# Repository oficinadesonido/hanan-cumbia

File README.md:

# HANAN CUMBIA · Batería electrónica (Arduino Nano)

Caja de ritmos / batería electrónica tropical de **Oficina de Sonido** (desde 2020). Plataforma
**Arduino Nano (ATmega328P)** + DAC externo **MCP4901** por SPI, síntesis por wavetable.
Dos versiones de hardware con **el mismo circuito y el mismo firmware**:

| Versión | PCB | Qué es |
|---|---|---|
| **Clásica** | `hardware/hananClasicaPcb/` | 77×92 mm, 8 pulsadores en placa, jack DC 9 V, va en caja. |
| **Mini** | `hardware/hananMiniPcb/` | 150×75 mm (= panel), calado para 4 botones arcade, se alimenta por USB. Para talleres. |

El rediseño 2026 en ESP32 es otro producto: `../hanan-mk2/`.

## 🔥 Web Flasher / Hanan Estudio

👉 **https://oficinadesonido.github.io/hanan-cumbia/webflasher/** (GitHub Pages desde `main`;
todo push a `main` queda publicado al toque). Chrome/Edge/Opera de escritorio (Web Serial).
`hananFabrica/` es el flasher de fábrica (solo firmware). Notas de diseño en `webflasher/README.md`.

## Estructura

```
hardware/hananClasicaPcb/   PCB clásica v2.0 (KiCad 10)      ← ver su README
hardware/hananMiniPcb/      PCB Mini v2.0 (KiCad 10)
firmware/hanan26Taller/     Firmware actual (Taller 2026; de acá salen los builds del Estudio)
firmware/tests/             Sketches de diagnóstico (DAC, potes, pines, motor de audio)
firmware/legacy/HTRCMB_10/  Firmware original del que deriva todo (histórico)
webflasher/                 Hanan Estudio + Lab + flasher (HTML/JS, STK500v1)
hananFabrica/               Flasher de fábrica
docs/                       Revisión eléctrica, capas EasyEDA, SVG de calados del panel Mini
```

Perfil de fabricación: **tht** (JLC solo PCB, se suelda en taller). Regla: toda placa lleva en silk
`<proyecto> vX.Y AAAA-MM-DD` = nombre del zip de gerbers (title block del PCB).

## Cambios v2.0 de ambas PCB (2026-10-07)
- RC en Vref del DAC (R6 1k + C2 10 µF) y 100 nF en Vdd (C3): el ruido del USB/cargador ya no entra
  directo a la referencia del audio. Pads del LED RGB agrandados. Rótulo de versión en silk.
- Mini: los 8 pads de los cables de los botones arcade pasan a una columna de pads grandes en pares
  (blanco/rosa/amarillo/verde + GND), zona GND en toda la placa.
- Detalle y pendientes en `docs/revision-electronica-mini.md` y `hardware/hananClasicaPcb/README.md`.

## Firmware: cambios respecto al original
- **Fix de tempo (pitch ⇒ BPM):** el secuenciador se clockeaba con `micros()`, que bajo la carga de la
  ISR de audio perdía tiempo. Ahora el tempo se cuenta con un reloj estable dentro de la ISR (`audioclock`).
- **BPM por defecto = 90**; **potenciómetros invertidos** (A0/A1); **A14 neutralizado** (solo 2 potes);
  **piso de pitch en A1** para que el sample siempre suene completo.

```bash
arduino-cli compile --fqbn arduino:avr:nano firmware/hanan26Taller
arduino-cli upload  --fqbn arduino:avr:nano -p /dev/ttyUSB0 firmware/hanan26Taller
```
Requiere el core `arduino:avr` y las librerías `Bounce` y `DAC_MCP49xx`.

## Historial
El material viejo (Placa_2021, HTR_2023, hanan25, audios, códigos, backups) se movió el 2026-10-07 a
`3-archivo/hanan-cumbia-historico/` (y está en el respaldo TOSHIBA). Repo viejo `oficinadesonido/HananCumbia` (2023).

---
🤖 Mantenido con ayuda de [Claude Code](https://claude.com/claude-code) · oficinadesonido.org

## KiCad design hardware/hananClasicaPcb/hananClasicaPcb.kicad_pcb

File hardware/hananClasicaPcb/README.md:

# hananClasicaPcb — Hanan Cumbia clásica, PCB principal v2.0 (2026-10-07)

Proyecto KiCad 10 armado el 2026-10-07 a partir de:
- **PCB:** `../hanan25.kicad_pcb` (77.1×92.1 mm; mismo diseño que `Hanan.kicad_pcb`/`Hanantaller.kicad_pcb`/`HTR_2023`;
  última fabricación JLC Y194, 10 u., 2025-11-14).
- **Esquemático:** copia de `hanan26/hananMiniPcb/hananMiniPcb.kicad_sch` (mismos refs y UUIDs que la PCB) +
  `J1` jack DC y `D2` diodo serie a `+9V`/VIN (net `VIN_JACK`). El `.sch` legacy `BD1.sch` queda como histórico.
  Los enlaces sch↔pcb coinciden (UUID de símbolo = path de huella), así que "Actualizar PCB desde esquemático" en el GUI
  no debería mover nada.

## Cambios v2.0 (iguales a hananMiniPcb v2.0)
- `R6` 1 kΩ + `C2` 10 µF: RC en Vref del MCP4901 (U1.6, net `VREF`); `C3` 100 nF en Vdd (U1.1). Cara B, borde izquierdo
  junto a R3 (R6 x=52.6, C2 x=51.8, C3 y=105.8). El +5C que entraba al pad 6 se cortó en (61.9,112.6) y se reruteó.
- Pads de `D1` (LED RGB) 1.25×1.8 mm (anillo 0.175 ≥ 0.13 JLC). Solo en la instancia del PCB.
- Title block (rev `v2.0`, fecha) + silk `hananClasicaPcb ${REVISION} ${ISSUE_DATE}` en F y B (y=160.6).
- DRC: 0 sin conectar, 0 errores. Warnings preexistentes: libs `OdeS`/`SWITCH`/`Arduino` no configuradas, silk al
  borde, textos XA1, vía colgada de `Net-(J2-Pad1)` en (113.3,149.7).

## Al fabricar
Fecha del title block = fecha de orden (sch y pcb) → zip `hananClasicaPcb-v2.0-<AAAA-MM-DD>.zip`.
Pendientes 🟡 (no incluidos): R serie en clock out, protección clock in, 10 nF de reconstrucción — ver
`hanan26/docs/revision-electronica-mini.md` (aplica igual a esta placa).

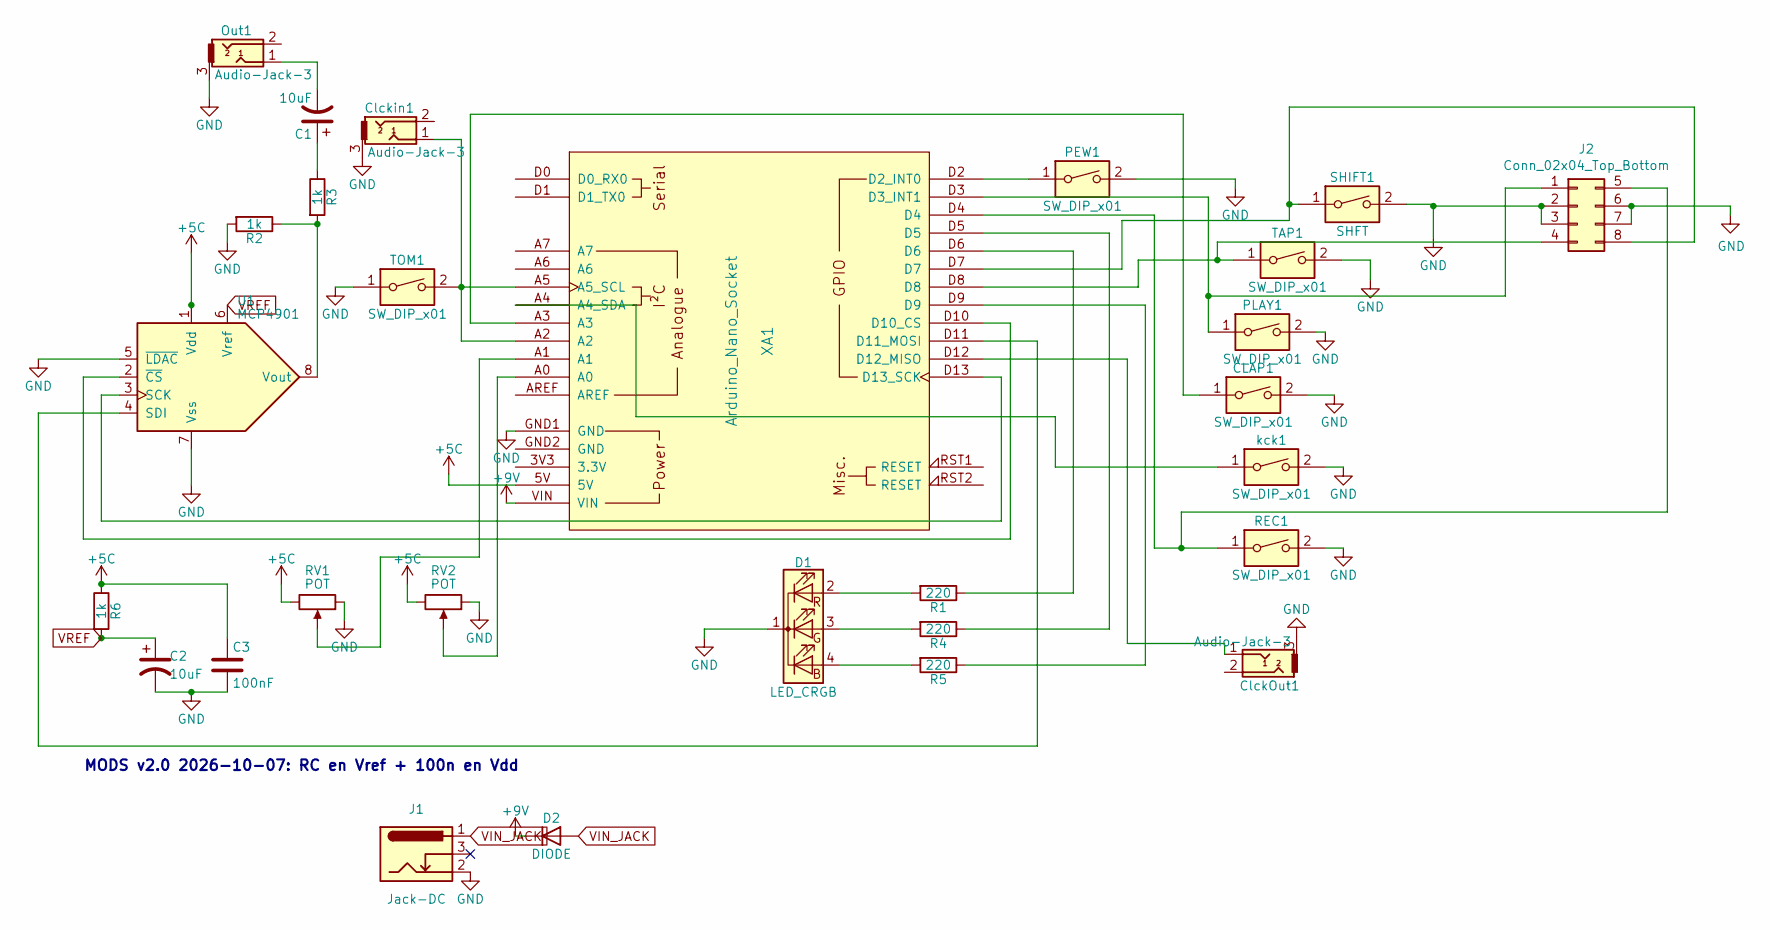
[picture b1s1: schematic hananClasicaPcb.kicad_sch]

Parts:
C1, C2: 10uF; CP_Radial_D4.0mm_P2.00mm
C3: 100nF; C_Disc_D5.0mm_W2.5mm_P5.00mm
CLAP1: SW_DIP_x01; SW_PUSH-12mm
ClckOut1: Audio-Jack-3; CONN_Jack_Female_3.5mm_THD
Clckin1: Audio-Jack-3; CONN_Jack_Female_3.5mm_THD
D1: LED_CRGB; LED_RGB_CATCOM_sep
D2: DIODE; D_A-405_P7.62mm_Horizontal
J1: Jack-DC; jack_dc_solder
J2: Conn_02x04_Top_Bottom; Hanan_PadsArcade_1x08_Pares_Compacto
Out1: Audio-Jack-3; CONN_Jack_Female_3.5mm_THD
PEW1: SW_DIP_x01; SW_PUSH-12mm
PLAY1: SW_DIP_x01; SW_PUSH_6mm
R1, R4, R5: 220; R_Axial_DIN0207_L6.3mm_D2.5mm_P7.62mm_Horizontal
R2, R3, R6: 1k; R_Axial_DIN0207_L6.3mm_D2.5mm_P7.62mm_Horizontal
REC1: SW_DIP_x01; SW_PUSH_6mm
RV1, RV2: POT; Potentiometer_Alps_RK09K_Single_Vertical
SHIFT1: SHFT; SW_PUSH_6mm
TAP1: SW_DIP_x01; SW_PUSH_6mm
TOM1: SW_DIP_x01; SW_PUSH-12mm
U1: MCP4901; DIP-8_W7.62mm_Socket_LongPads
XA1: Arduino_Nano_Socket
kck1: SW_DIP_x01; SW_PUSH-12mm

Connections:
+5C: C3.1, R6.1, RV1.3, RV2.3, U1.1 (Vdd), XA1.5V
+9V: D2.1 (K), XA1.VIN
GND: C2.2, C3.2, CLAP1.2, ClckOut1.3, Clckin1.3, D1.1 (K), J1.2, J2.2, J2.3, J2.6, J2.7, Out1.3, PEW1.2, PLAY1.2, R2.2, REC1.2, RV1.1, RV2.1, SHIFT1.2, TAP1.2, TOM1.1, U1.5 (~LDAC), U1.7 (Vss), XA1.GND1 (GND), kck1.2
unnamed: C1.1, R3.1
unnamed: C1.2, Out1.1
unnamed: CLAP1.1, XA1.A3
unnamed: ClckOut1.1, XA1.D12 (D12_MISO)
unnamed: D1.2 (RA), R1.2
unnamed: D1.3 (GA), R4.2
unnamed: D1.4 (BA), R5.2
unnamed: D2.2 (A), J1.1
unnamed: J2.1, PLAY1.1, XA1.D3 (D3_INT1)
unnamed: J2.4, TAP1.1, XA1.D8
unnamed: J2.5, REC1.1, XA1.D4
unnamed: J2.8, SHIFT1.1, XA1.D7
unnamed: PEW1.1, XA1.D2 (D2_INT0)
unnamed: R1.1, XA1.D6
unnamed: R2.1, R3.2, U1.8 (Vout)
unnamed: R4.1, XA1.D5
unnamed: R5.1, XA1.D9
unnamed: RV1.2, XA1.A1
unnamed: RV2.2, XA1.A0
unnamed: U1.2 (~CS), XA1.D10 (D10_CS)
unnamed: U1.3 (SCK), XA1.D13 (D13_SCK)
unnamed: U1.4 (SDI), XA1.D11 (D11_MOSI)
unnamed: XA1.A4 (A4_SDA), kck1.1
VREF: C2.1, R6.2, U1.6 (Vref)

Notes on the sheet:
MODS v2.0 2026-10-07: RC en Vref + 100n en Vdd

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
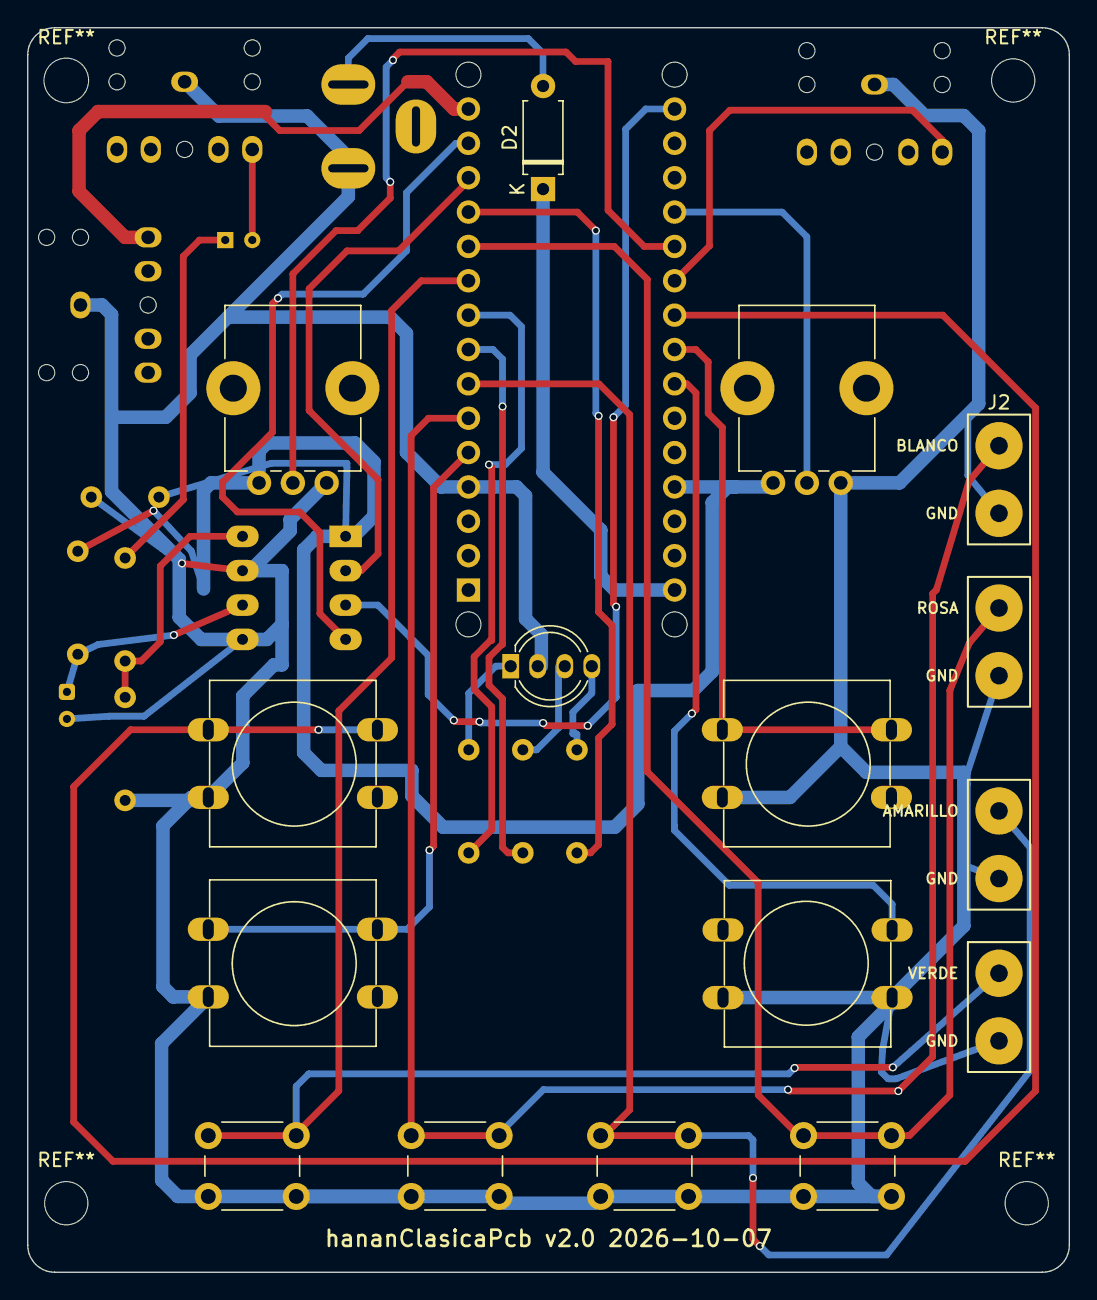
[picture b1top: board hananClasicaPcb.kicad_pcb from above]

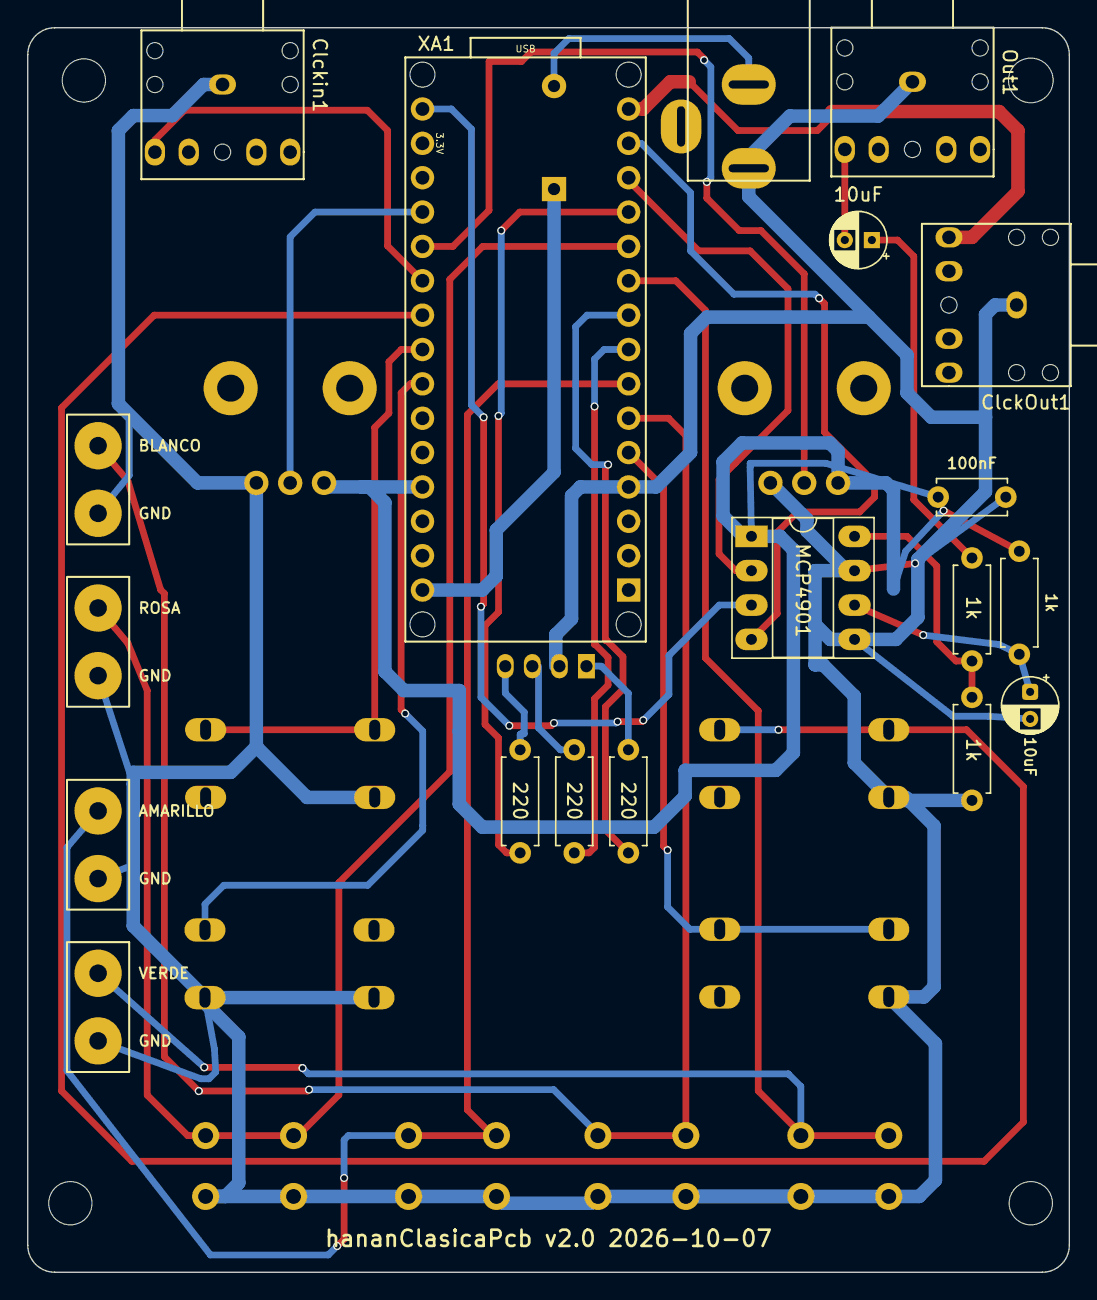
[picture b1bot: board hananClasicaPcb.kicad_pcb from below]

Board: 2 copper layers, 77.0 x 92.0 mm, 28 parts (15 on the bottom side), 29 nets.
